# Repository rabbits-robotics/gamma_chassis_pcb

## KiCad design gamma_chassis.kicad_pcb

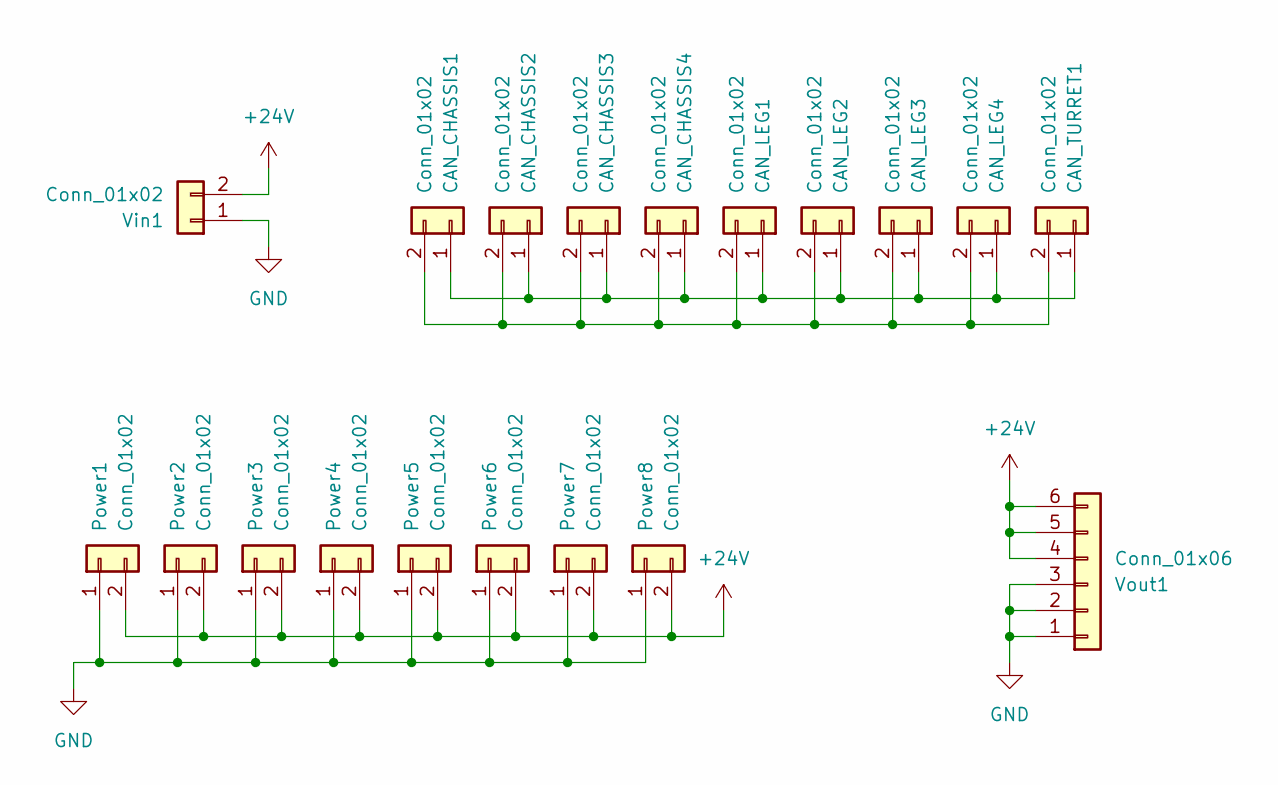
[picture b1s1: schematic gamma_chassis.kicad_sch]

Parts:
CAN_CHASSIS1, CAN_CHASSIS2, CAN_CHASSIS3, CAN_CHASSIS4: Conn_01x02; JST_PH_B2B-PH-K_1x02_P2.00mm_Vertical
CAN_LEG1, CAN_LEG2, CAN_LEG3, CAN_LEG4: Conn_01x02; JST_PH_B2B-PH-K_1x02_P2.00mm_Vertical
CAN_TURRET1: Conn_01x02; JST_PH_B2B-PH-K_1x02_P2.00mm_Vertical
Power1, Power2, Power3, Power4, Power5, Power6, Power7, Power8: Conn_01x02; AMASS_XT30U-F_1x02_P5.0mm_Vertical
Vin1: Conn_01x02; AMASS_XT30PW-M_1x02_P2.50mm_Horizontal
Vout1: Conn_01x06; JST_PH_B6B-PH-K_1x06_P2.00mm_Vertical

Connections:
+24V: Power1.2, Power2.2, Power3.2, Power4.2, Power5.2, Power6.2, Power7.2, Power8.2, Vin1.2, Vout1.4, Vout1.5, Vout1.6
GND: Power1.1, Power2.1, Power3.1, Power4.1, Power5.1, Power6.1, Power7.1, Power8.1, Vin1.1, Vout1.1, Vout1.2, Vout1.3
unnamed: CAN_CHASSIS1.1, CAN_CHASSIS2.1, CAN_CHASSIS3.1, CAN_CHASSIS4.1, CAN_LEG1.1, CAN_LEG2.1, CAN_LEG3.1, CAN_LEG4.1, CAN_TURRET1.1
unnamed: CAN_CHASSIS1.2, CAN_CHASSIS2.2, CAN_CHASSIS3.2, CAN_CHASSIS4.2, CAN_LEG1.2, CAN_LEG2.2, CAN_LEG3.2, CAN_LEG4.2, CAN_TURRET1.2

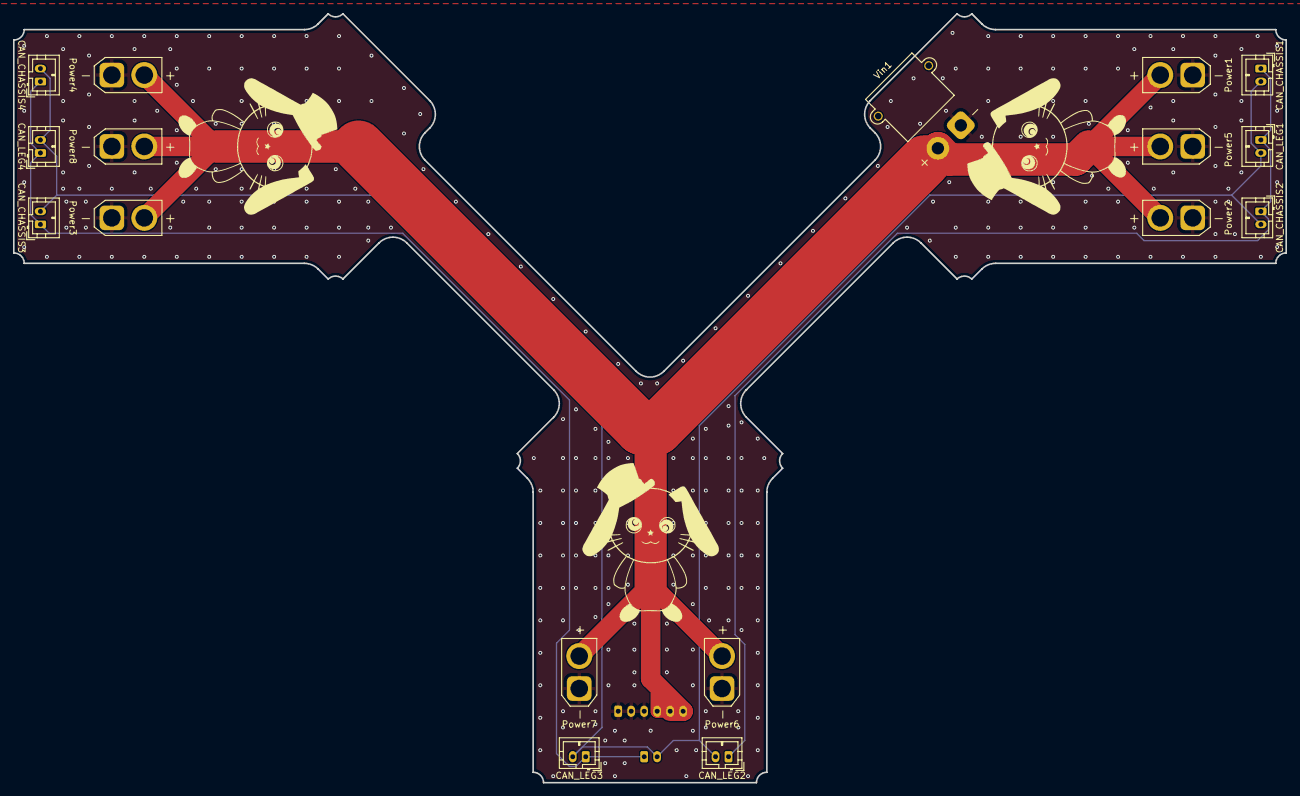
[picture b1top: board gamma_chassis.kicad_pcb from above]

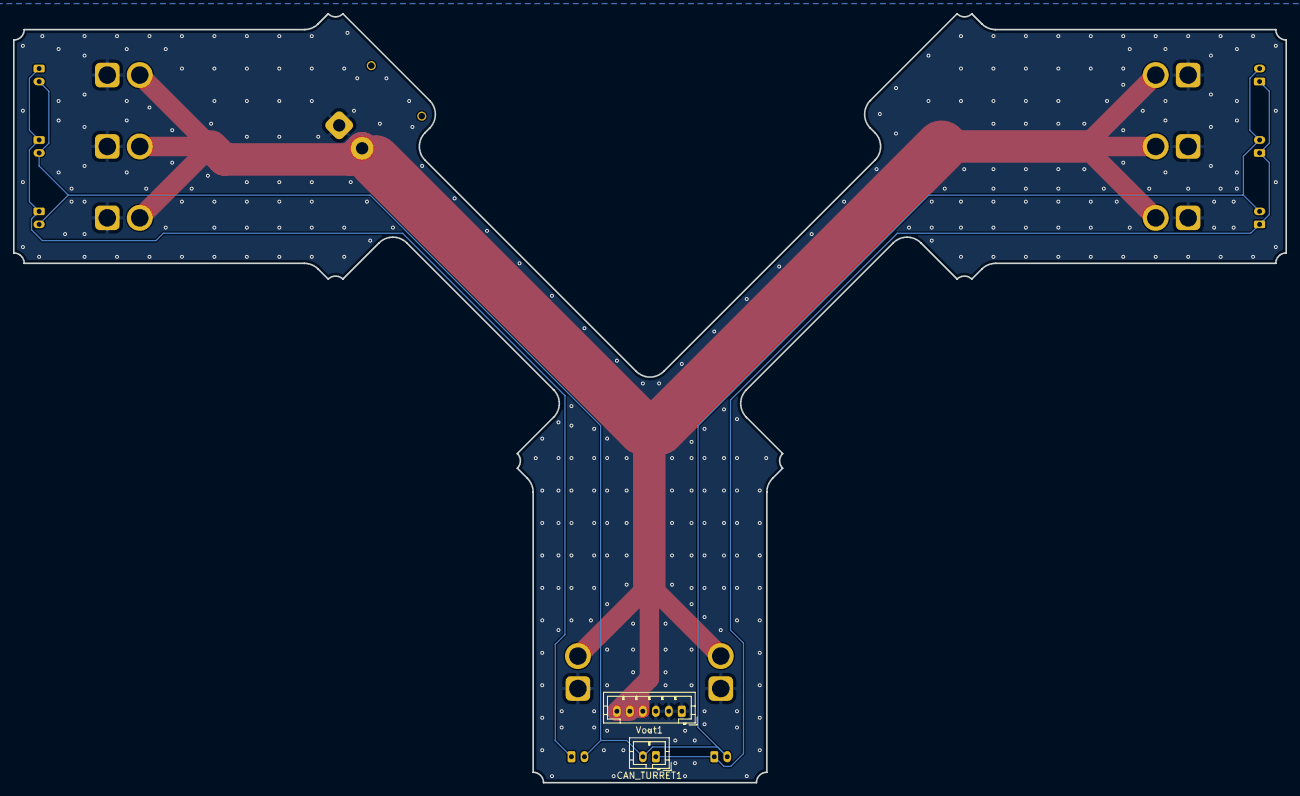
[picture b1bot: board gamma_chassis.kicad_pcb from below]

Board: 2 copper layers, 196.0 x 118.4 mm, 19 parts (2 on the bottom side), 4 nets.

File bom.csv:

"Reference","Value","Footprint","QUANTITY"
"CAN_CHASSIS1-CAN_CHASSIS4,CAN_LEG1-CAN_LEG4,CAN_TURRET1","Conn_01x02","Connector_JST:JST_PH_B2B-PH-K_1x02_P2.00mm_Vertical","9"
"Power1-Power8","Conn_01x02","Connector_AMASS:AMASS_XT30U-F_1x02_P5.0mm_Vertical","8"
"Vin1","Conn_01x02","Connector_AMASS:AMASS_XT30PW-M_1x02_P2.50mm_Horizontal","1"
"Vout1","Conn_01x06","Connector_JST:JST_PH_B6B-PH-K_1x06_P2.00mm_Vertical","1"
